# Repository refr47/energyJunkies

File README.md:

# Content

Es soll ein Produkt (HW, SW) geschaffen werden, welches analog dem [Ohmpilot von Fronius](https://www.fronius.com/de/solarenergie/installateure-partner/technische-daten/alle-produkte/l%C3%B6sungen/fronius-w%C3%A4rmel%C3%B6sung/fronius-ohmpilot/fronius-ohmpilot) funktioniert. Damit soll überschüssiger PV-Strom hausintern verbraucht werden (z.B. Warmwasseraufbereitung). Als Steuerzentrale wird ein uController - [esp32 mit kleinem Display](https://www.lilygo.cc/products/lilygo%C2%AE-ttgo-t-display-1-14-inch-lcd-esp32-control-board) - herangezogen. Dieser ESP ist mit WLAN und Bluetooth ausgestattet. Als ReferenzWR werden Fronius-WR herangezogen, wobei hier der Modbuszugang freizuschalten ist. 

## Installation /InBetriebnahme / Fehler
Unter [https://github.com/htlWels/energyJunkies/blob/main/projects/sware/ohmPilotFronius/doc/install.md] ist eine Installationsanleitung zu finden, welche die einzelnen Schritte für eine erfolgreiche Installation Schritt für Schritt erläutert.
Es können natürlich noch Fehler oder seltsames Verhalten auftreten. Diese könnten unter [https://github.com/htlWels/energyJunkies/blob/main/projects/sware/ohmPilotFronius/doc/error.md] dokumentiert werden und werden dann behoben. 

## Versionsverwaltung per GIT
Die installierbaren Versionen werden im "main"-Branch verwaltet und die Erweiterungen in einem separaten Branch. Nach einem erfolgreichen Test werden dann die Branches wieder in den Main-Branch integriert und die Version wird dann erhöht. Es wird mit der Version v0.9 bekommen

- Branch main: Basisfunktionalität (Heizstab-Regler mit Untersützung des Fronius-WR und AMIS-Reader (Siemens TD3511 Smartmeter), Temperaturüberwachung, minimaler Shelly-Support
- Branch shelly: Experimentielles im Umgang  mit Shelly-Produkten
- Branch enj: Testumgebung für ENJ für das Austesten der 4 Buttons
- Branch Powerregulation: kl. Beispiel von Bernhard für pid-Regler
- Branch loxone: Erweiterung des REST-Interfaces für Einbindung Loxone-Verwaltung, Reduzierung des Codes auf die Ansteuerung der Platine, kein Modbus/Fronius/amisReader-Support

## Anforderungen

Das Produkt wird in einen hardware- und softwareabhängigen Teil aufgespaltet. Es ist ein "Hobby"-Projekt, aber dennoch sollten die wesentlichen Anforderungen erfasst werden. Prinzipiell wird davon ausgegangen, dass die zu betreibenden Heiz/Lade -elemente einen 3-phasigen Anschluß haben, die dann einzeln angesteuert werden.

### HW

Der OhmPilot von Fronius kann dzt. um die gut € 1.000,-- erworben werden, d.h. die Entwicklungskosten für die HW sollten deutlich unterschritten werden (!)

* Die GPIOs des ESP32 werden mit 3.3 V betrieben. Über eine entsprechende TransistorSchaltung kann je Phase dann per Relais durchgeschaltet werden. Alternativ könnte ein Pegelwandler 3.3V auf 5V genutzt werdenererer
* 2 Temperatursensoren sorgen für einen "Not-Aus", d.h. wenn beispielsweise das Wasser schon 85° hat, darf nicht mehr geheizt werden. Sicherheitshalber werden 2 Sensoren verwendet für den Fall, dass einer ausfällt. Die gesteuerte Last könnte auch indirekt über ein Sicherheitsthermostat indirekt angeschlossen werden.
* Lage des Displays (vertikal | horizontal) ?
* Vorschläge von Ej - Blockschaltbilder liegen in **projects/ohmPilotFronius/**
* EJ-EMV Filter (Elektromagnetischer Filtervorsatz, auf diesen wird in der ersten Phase verzichtet bzw. Vorversuche gestartet)
-  EJ-Control Board (ESP32 TTGO, Eingabe, Ausgabe Schnittstellen, Versorgt über die Power Unit)
-  EJ-Power Unit1 (Phasenanschnitt mit Modul 2-10V vom Armin bzw. Modul 0-20mA vom Oliver, sehr große EMV Probleme, erste Hardware für Versuche)
-  EJ-Power Unit2 (PWM Endstufe, eventuell Schülerprojekt 23/24, große EMV Probleme)
-  EJ-Power Unit3 (Pulspakete, eventuell Schülerprojekt 23/24, wenig EMV Probleme, AMIS Zähler?)
-  EJ-Power Unit4 (eine Art 7 Takt Schaltung wie bei den alten E-Herd Platten, sehr wenig EMV Probleme, keine stufenlose Regelung)

#### Verbesserungsvorschläge
- Rote LED, welche eine Warnung/Fehler anzeigt; dieser wird zusätzlich am Display angezeigt
- die dzt. 4 Taster sollten mit einer Brücke einstellbar sein ; somit stehen 4 GPIOs zur Verfügung, die anderweitig eingesetzt werden können (potentialfreie Ausgänge, über Buchse ausführen
- PWM Verbindung herstellen (bei neuer Platine)
- 4 Schalter abänderung und verwenden für
  * S1: Zustands-/Fehler LED
  * S2: Relais ausführen
  * S3/S4: eventuell die anderen 2 auch als potentialfreien Ausgang ausführen (Relais)
- Shelly Einbindung (reine SW)

### SW

* Setup: Folgende Parameter sind benutzer- bzw. analagenabhängig:
  - Einstellung der WLAN-Zugangsdaten (SSID,Password)
  - IP-Adresse Modbus
  - Heizstableistung (für die rechnerische Festlegung der in das Heizsystem geleiteten Energie)
  - Einspeisebeschränkung (wieviel kW dürfen eingespeist werden)
 -  <del>PI-Regler für den 0-100 % Ausgang (Proportional(P),Integral(I),Differenzial(D)) - Default: P=1, I=0.5, D=0 (FLoat)</del>
  - <del>Regelbereich Hysterese für die PWM-Steuerung (z.B. 5.900, 5.800 - Hysterese: 100) - oder von Einspeisebeschränkung 100 Watt abziehen und Hysteresewert </del>
  - Für die Eingabe ist eine WebSite zu verwenden, wobei der uController (ESP32) bei der Erst-Inbetriebnahme oder Wechsel des Wlan-Einwählpunktes als AccessPoint fungiert. Die notwendigen Informationen (SSID,IP-Adresse) sind per Display anzuzeigen.
  - Die Setup-Basisdaten sind per EEProm zu sichern, die bei einem Restart dann herangezogen werden können. 
* Auf dem Display sollten die wichtigsten Informationen angezeigt werden können:
  - aktive Netzwerkverbindung
  - IP-Adresse
  - aktuelle Produktion, davon Überschuss
  - Zuteilung an die 3 Phasen
  - aktuelle Temperatur des Wasses, gemessen durch die 2 TempSensoren
  - Fehler
  - ?
* Die Kommunikation wird per WLAN durchgeführt, wobei regelmäßig zu prüfen ist, ob die WLAN-Verbindung noch funktioniert
  - ?? hat nur tagsüber Sinn
  - was passiert, wenn die Kommunikation nicht mehr funktioniert - Fehlermeldung am Display ( ! ), Abschalten des Reglers für den Heizstab
- Der WR wird per Modbus (TCP) angesteuert & setzt eine funktionierende WLAN-Verbindung voraus.
- Alternativ kann auch der AmisReader verwendet werden, wobei hier weniger Informationen zur Verfügung stehen. 
- Da Fronius bei der kostenlosen Variante die Verbrauchsdaten nur für 3 Tage loggt, kann der ESP32 diese mitloggen. Dafür ist jedoch ein CardReader notwendig.
- kleines REST-API, wo die wichtigsten Daten per Web verfügbar sind, die IP-Adresse steht ja auf dem DIsplay.
- Benachrichtigung per Email, dass irgend etwas passiert ist ( ? )
- Der Regler muss bei Erreichen des Temperaturlimits (per Setup-Dialog einstellbar) sämtliche Kanäle abschalten.
- Sofern ein Akku vorhanden ist, soll die Priorisierung einstellbar sein (d.h. wird zuerst der Boiler oder der Akku geladen).

## Offene Fragen
* Initialisierung/sETUP: Wenn Netzwerk nicht funktioniert, kommt man automatisch in den AccessPoint-Modus;
* ```Wenn beim Setup kein gültiges WLAN-Netzwerk vorgefunden wird, bootet der ESP32 im AP-Modus mit der Default-Adresse 192.168.4.1 und bietet dazu auch einen offenen Zugang namens "EnergyJunkies" an.```
* Was macht man bei auftretenden Fehlern?
* ```Diese werden sowohl am Display als auch am Web-Interface angezeigt.```

## Was einem sonst noch so einfällt

* Bezüglich Tag/Nacht-Betrieb: Prinzipiell macht die Steuerung nur dann Sinn, wenn Strom produziert wird -also tagsüber. Wahrscheinlich werden künftig unterschiedliche h-Strompreise angeboten werden, d.h. bei schönem Wetter ist mehr Solarstrom da und daher günstiger ( ? ) oder der Strom ist dann teuerer, wenn mehr gebraucht wird (z.B. vormittags). Einen Boiler muss man immer betreiben und hier könnte es Sinn machen, auch einen Nachtbetrieb einzuführen, da hier der Strom wahrscheilich günstiger ist.
* Es wäre für die Optimierung der Energiekosten (welcher Tarif ist für das Aufheizen/Aufladen am günstigsten) günstig, wenn man den Wetterbericht kennt, denn dann weiß man ja, ob genug Solarstrom vorhanden ist, den Task durchzuführen (z.B. Aufladen).
* Künftig werden wahrscheinlich variable Einspeistarife vorgegeben werden, variable Stromkosten für den Einkauf gibt es ja schon. Hier kann dann optimiert werden in Abstimmung mit einem eventuell vorhandenen Akku, wann wer wie geladen / in das Netz gespeist wird.
* Poolpumpe bzw. Poolwärmepumpe: Poolpumpe wälzt das Wasser im Becken um, egal welche Qualität das Wasser hat. Hier könnte in Verbindung mit einem Frequenzumformer die Leistung der Pumpe reduziert werden, wenn man weiß, welche Qualität das Wasser dzt. hat. Die Wärmepumpe kann ebenfalls in Abhängigkeit von Überstrom gesteuert werden (Ein- bzw. Ausschalten per TCP?)
* Setup: Jeder hat ja seine eigen Zugangsdaten - wie sollen diese am Besten berücksichtigt werden. Der geringste Aufwand ist die Erstellung eines eigenen setup.h-Files, in der sämtliche spezifische Daten eingetragen werden. Elegant wäre natürlich das Setup per Handy, wobei der ESP im Setup-Modus bootet und einen eigenen AP zur Verfügung stellt, in der sich eine App einwählt und dann die Zugangsdaten einstellt. Diese Daten werden dann ins Eprom verfrachtet - ``Ẁird so durchgeführt``
* Im Prototyp sind ja 4 zusätzliche Taster vorgesehen - es ist hier zu definieren, welche Funktionalität hier hinterlegt wird.
* Thema WLAN/Setup: ich hab bereits ein Projekt mit einem ESP2866 am Start und genau diese Problematik. Ich hab 2 Bibliotheken im Einsatz: 
  - [WIFI-Manager](https://github.com/tzapu/WiFiManager) Hotspot + Webserver für WLAN Konfiguration + eigenes Setup möglich (ums Speichern des eigenen Setups muss man sich selbst kümmern)
  * [WebConfig](https://github.com/GerLech/WebConfig)eigener Webserver ausschließlich für Konfiguration, Daten werden am FS gespeichert
* HomeKit Integration: ich hab bereits etliche Geräte mit Apple HomeKit im Einsatz und auch schon eigene Geräte HomeKit tauglich gemacht. Meine Idee wäre, einfach einen Schalter mit einem ESP zu simulieren (z.B. Stromüberproduktion-> Schalter ist ON, ...) Dieser Schalter lässt sich easy in die bestehende Infrastruktur einbinden und dank Homekit können dann eigene Abläufe konfiguriert werden -> "Schalter Stromüberproduktion" = ON -> schalte über einen Shelly (ebenfalls mit Homekit Firmware geflasht) den Warmwasserboiler ein. ```Zum Verständnis: HomeKit frägt die Steuerung periodisch ab und gibt dann - je nach vorhandenem Strom - ein "On" oder "Off" zurück - Schwelle für "On" (also wieviel (k)Watt) ist einstellbar```
* Shelly-Support: Die Shelly-Infrastruktur ist bezüglich Wachstum recht viral und Shelly bietet neben einer funktionierenden App auch ein REST- und MQTT-Interface an. Shelly brauchen eine intakte WLAN-Verbindung und schalten ab, wenn kein Netzwerk verfügbar ist (z.B. Abschalten während der Nachtstunden). Man muss Shelly dann manuell per App einschalten - ein Reconnect wird dzt. nicht unterstützt. 

# IDE/PlatformIO

<ol>
    <li>[C/C++ COmpiler mit Platformio](https://alsaibie.github.io/embedded_ccpp/ide_setups/pio_for_host/)
    </li>
</ol>
## Links & Foren
<ol>
<li>
Photovoltaik Form [Photovoltaik Form](https://www.photovoltaikforum.com/thread/50214-gen24-modbus-tcp/)
</li>
    <li>
        [TTGO ESP] (https://www.lilygo.cc/products/lilygo%C2%AE-ttgo-t-display-1-14-inch-lcd-esp32-control-board)
    </li>
    <li>
        Mark Down Formatierung (https://www.markdownguide.org/cheat-sheet/#extended-syntax)
    </li>

</ol>

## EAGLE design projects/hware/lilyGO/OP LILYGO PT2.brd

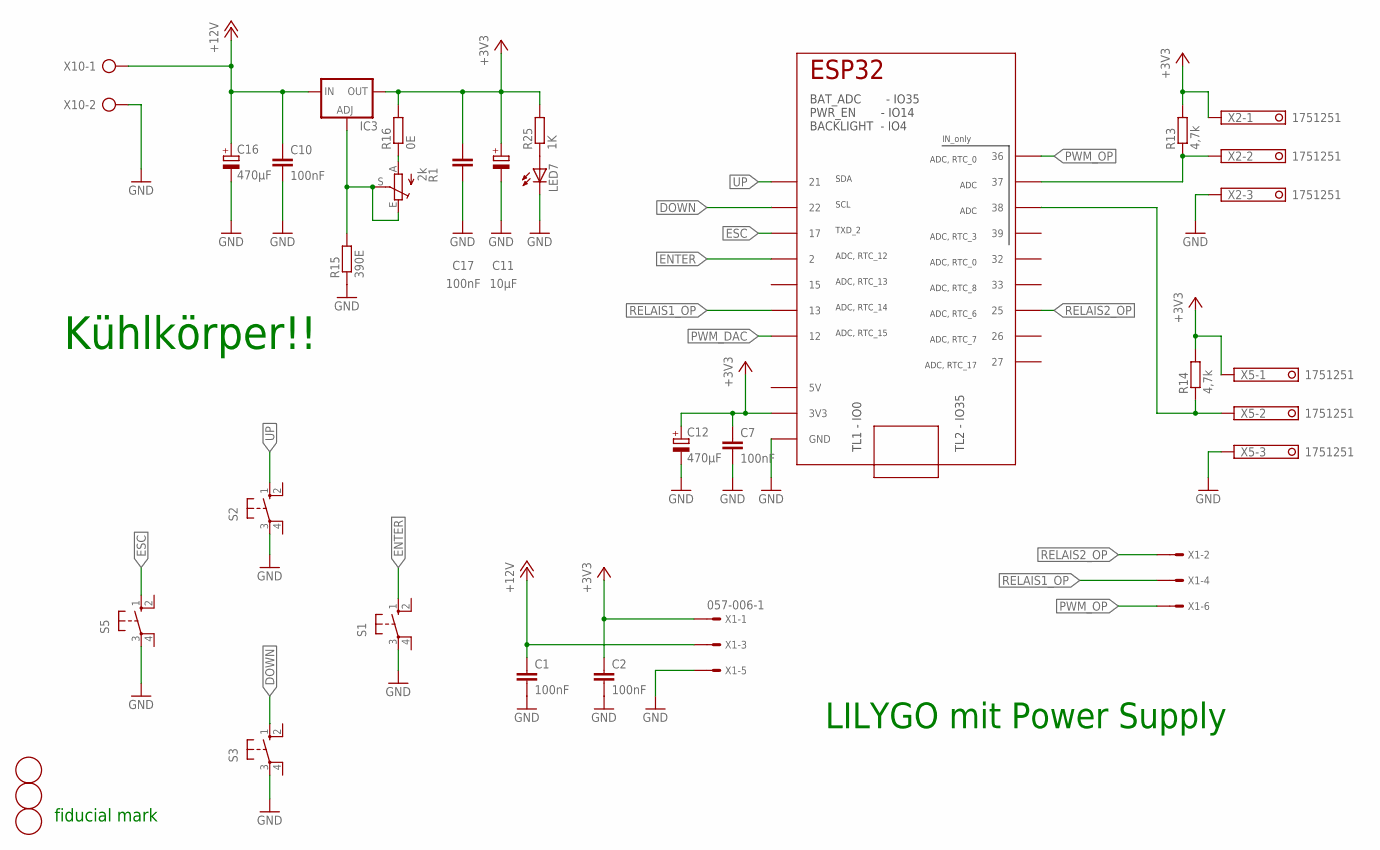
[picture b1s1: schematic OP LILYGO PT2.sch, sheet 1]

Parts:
C1, C2, C7, C10, C17: 100nF; C025-030X050
C11: 10µF; E2,5-6
C12, C16: 470µF; E2,5-6
IC3: LM317TS; 317TS
IC4: TTGO_DISP; TTGO_DISP_DEFAULT
LED7: LED5MM
R1: 2k; S64YW
R13, R14: 4,7k; 0207/12
R15: 390E; 0207/12
R16: 0E; 0207/12
R25: 1K; 0207/12
S1, S2, S3, S5: 10-XX; B3F-10XX
U$2, U$7, U$8: FIDUCIALMOUNT; FIDUCIA-MOUNT
X1: 057-006-1
X2, X5: 1751251
X10: SMKDSP_1,5/2

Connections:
+3V3: C2.1, C7.1, C11.+, C12.+, C17.1, IC3.2 (OUT), IC4.3V3_1 (3V3), IC4.3V3_2 (3V3), R13.2, R14.2, R16.2, R25.2, X1.1, X2.1, X5.1
+12V: C1.1, C10.1, C16.+, IC3.3 (IN), X1.3, X10.1; also elsewhere on the board
DOWN: IC4.22, S3.1 (S)
ENTER: IC4.2, S1.1 (S)
ESC: IC4.17, S5.1 (S)
GND: C1.2, C2.2, C7.2, C10.2, C11.-, C12.-, C16.-, C17.2, IC4.GND_1 (GND), IC4.GND_2 (GND), IC4.GND_3 (GND), IC4.GND_4 (GND), IC4.GND_5 (GND), LED7.K (C), R15.1, S1.3, S2.3, S3.3, S5.3, X1.5, X2.3, X5.3, X10.2; also elsewhere on the board
unnamed: IC3.1 (ADJ), R1.E, R1.S, R15.2
unnamed: R1.A, R16.1
unnamed: IC4.37, R13.1, X2.2
unnamed: IC4.38, R14.1, X5.2
unnamed: LED7.A, R25.1
PWM_DAC: IC4.12; also elsewhere on the board
PWM_OP: IC4.36, X1.6
RELAIS1_OP: IC4.13, X1.4
RELAIS2_OP: IC4.25, X1.2
UP: IC4.21, S2.1 (S)

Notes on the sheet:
LILYGO mit Power Supply
fiducial mark
Kühlkörper!!

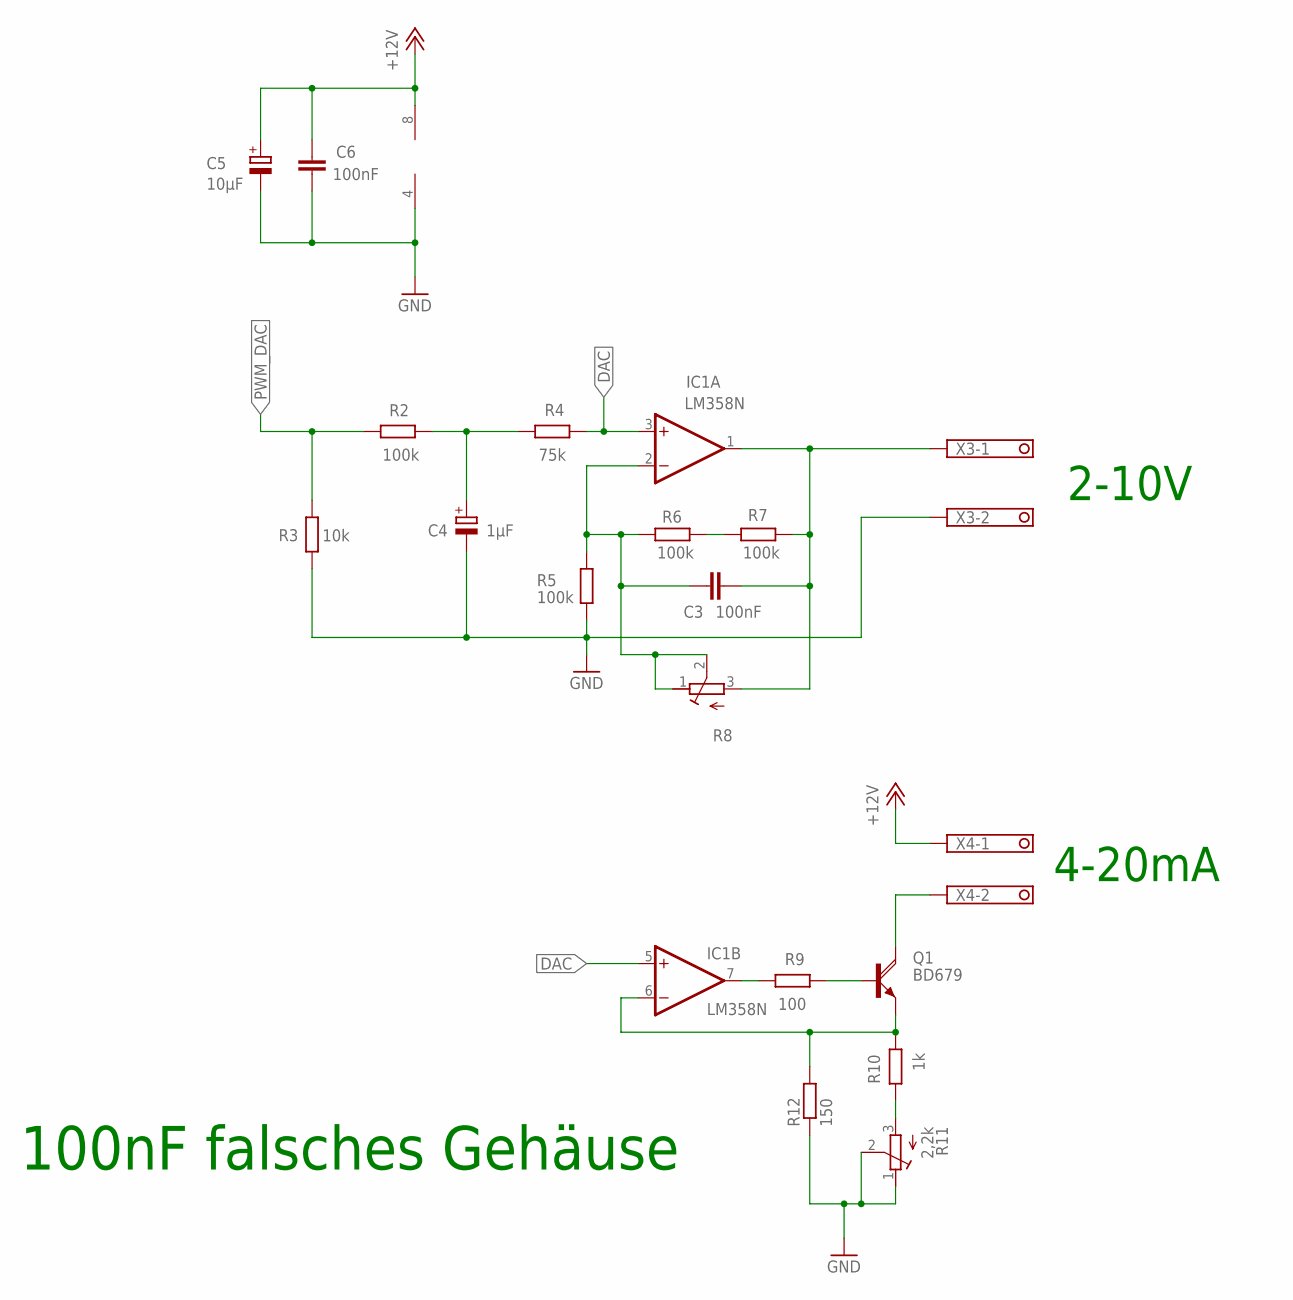
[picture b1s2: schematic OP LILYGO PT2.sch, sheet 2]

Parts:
C3, C6: 100nF; C050-035X075
C4: 1µF; E2,5-5
C5: 10µF; E2,5-5
IC1: LM358N; DIL08
Q1: BD679; TO126AV
R2, R5, R6, R7: 100k; 0207/2V
R3: 10k; 0207/2V
R4: 75k; 0207/2V
R8: R-TRIMMT93YA; RTRIMT93YA
R9: 100; 0207/10
R10: 1k; 0207/2V
R11: 2,2k; RTRIMT93YA
R12: 150; 0207/12
X3, X4: 1751248

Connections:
+12V: C5.+, C6.1, IC1.8 (V+), X4.1; also elsewhere on the board
DAC: IC1.3 (+IN), IC1.5 (+IN), R4.1
GND: C4.-, C5.-, C6.2, IC1.4 (V-), R3.1, R5.2, R11.1 (E), R11.2 (S), R12.1, X3.2; also elsewhere on the board
unnamed: C3.1, IC1.2 (-IN), R5.1, R6.1, R8.1 (E), R8.2 (S)
unnamed: C4.+, R2.2, R4.2
unnamed: R10.2, R11.3 (A)
unnamed: C3.2, IC1.1 (OUT), R7.2, R8.3 (A), X3.1
unnamed: R6.2, R7.1
unnamed: IC1.6 (-IN), Q1.E, R10.1, R12.2
unnamed: Q1.B, R9.1
unnamed: IC1.7 (OUT), R9.2
unnamed: Q1.C, X4.2
PWM_DAC: R2.1, R3.2; also elsewhere on the board

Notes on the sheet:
2-10V
4-20mA
100nF falsches Gehäuse

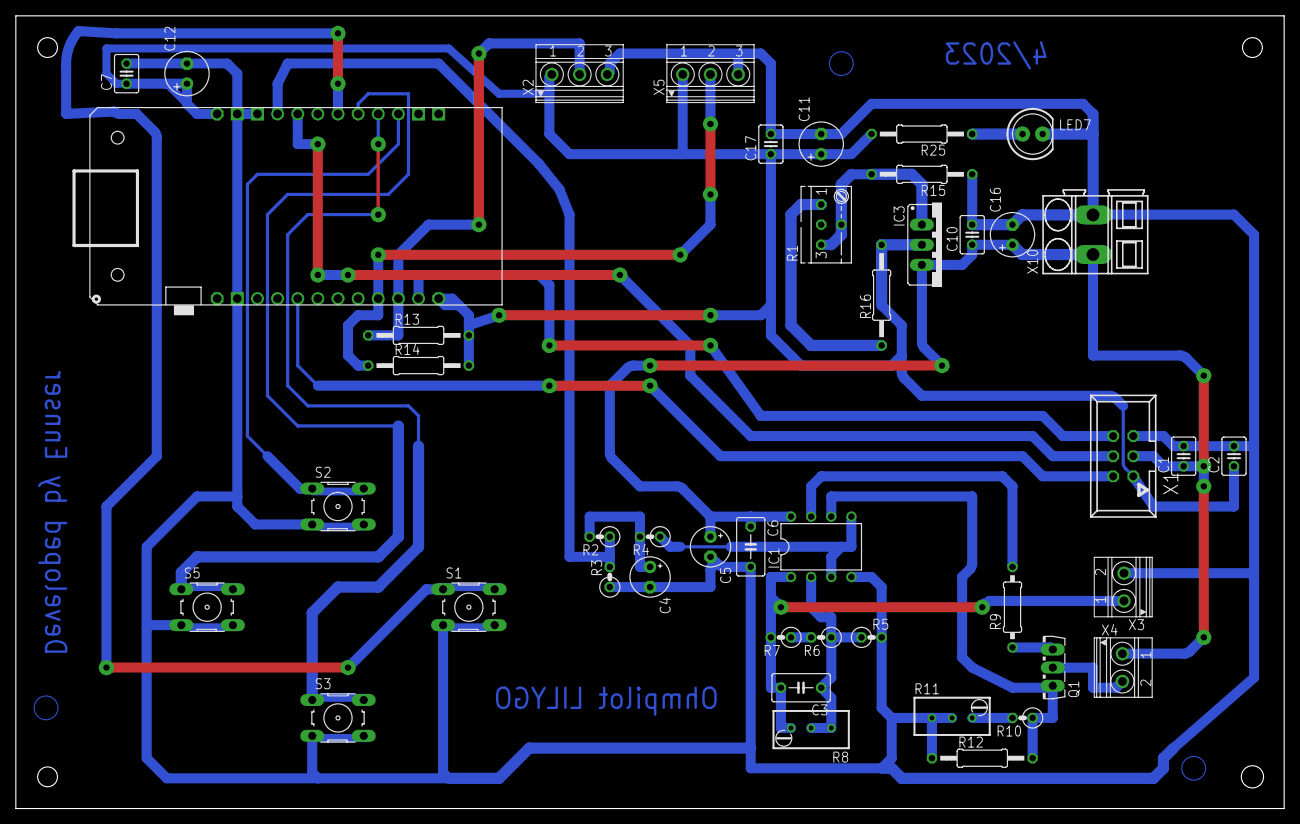
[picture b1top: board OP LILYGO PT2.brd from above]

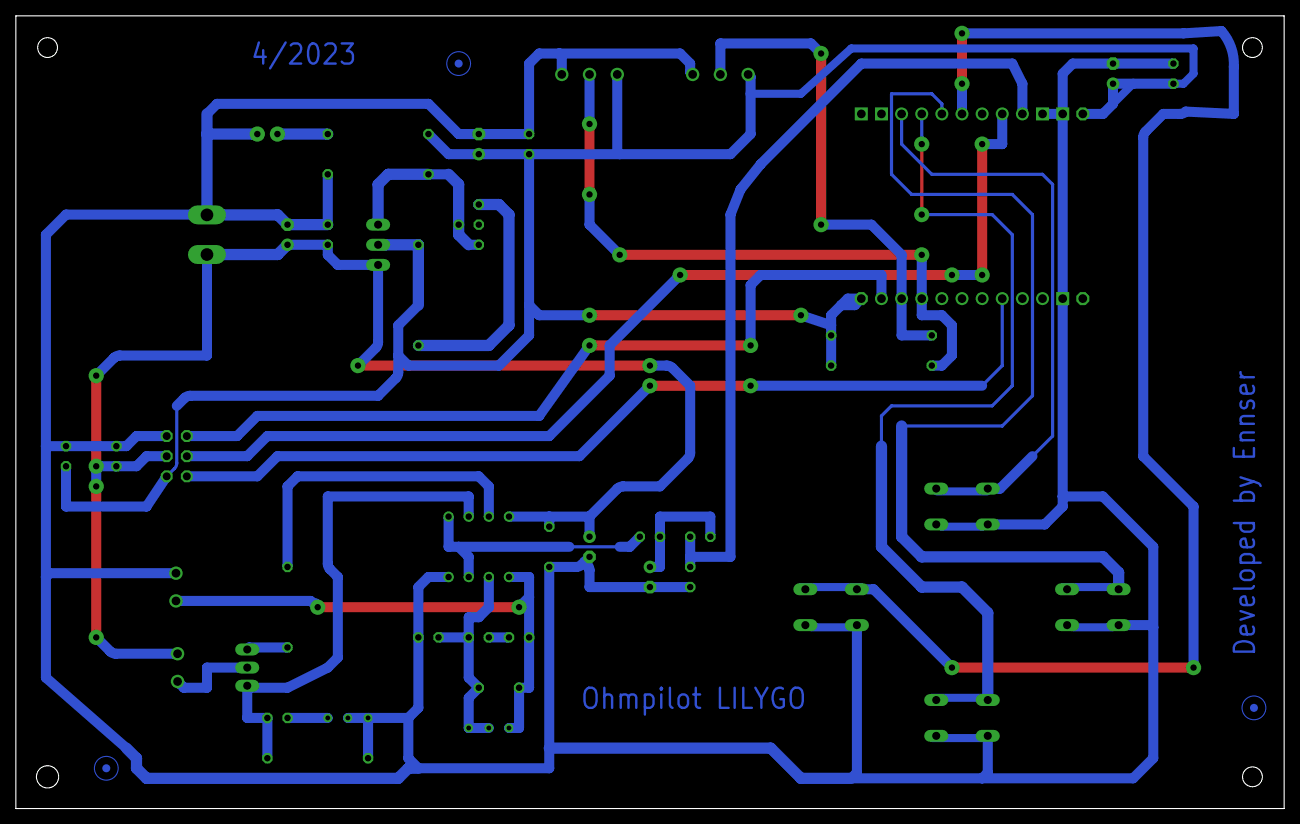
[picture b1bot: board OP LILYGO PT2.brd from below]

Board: 2 copper layers, 160.0 x 100.0 mm, 47 parts (3 on the bottom side), 26 nets.

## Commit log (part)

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2024-02-02 controller
2024-02-02 huawei
2024-02-02 fronius
2024-02-04 amisReader
2024-02-04 amis
2024-02-05 websock
2024-02-05 main
2024-02-06 setup
2024-02-07 states
2024-02-07 solar
2024-02-12 defines/remove string
2024-02-15 sockets
2024-02-19 debug
2024-02-19 bugfix, debugger
2024-02-21 froniusSolar
2024-02-21 socket
2024-02-21 bug fix
2024-02-21 output.js
2024-02-22 defines
2024-02-22 index
2024-02-23 energieManager
2024-03-14 http-get-request
2024-03-20 wheater
2024-04-21 eeprom
2024-04-23 eprom
2024-04-25 utils
2024-04-26 pidManager
2024-04-29 temp
2024-05-10 heap
2024-05-10 wwww
2024-05-12 wlan
2024-05-12 nain
2024-05-13 shelly
2024-05-13 install
2024-05-13 install.md
2024-05-13 error
2024-05-19 Doku
2024-05-22 logReader
2024-05-22 logWWW
2024-05-22 logswww
2024-05-31 esp log lib
2024-07-09 'NetzOOE-Export zu Lastprofil'-Generator
    Skript erzeugt aus einem Viertelstunden-Protokoll (z.B. von Netz OÖ) ein Lastprofil für z.B. den Tarifkalkulator der E-CONTROL.
2024-07-26 shelly,web
2024-07-26 shelly-eprom
2024-07-26 amisReader / interpretation output pidController
2024-07-26 docker
2024-07-26 merge
2024-07-26 script
2024-08-03 fixError(wlan,pidManager)
2024-08-04 fixError
2024-08-12 mqtt
2024-08-22 reconnect
2024-10-10 temp sensor
2024-10-11 loxone
2024-10-11 ajax
2025-06-07 tempenumberOfDevicesratur
2025-06-07 oneWire
2025-08-03 temperature control
2025-08-04 overflow temperature
2025-08-29 refactor: clean up code structure and improve readability
2025-08-30 ajaxCall,update, strncpy
2025-08-31 pidmanager, reset, clear pwm
2025-09-02 amisreader,websocket: error fixing
2025-09-02 ajaxCall,handle_store as callback from update stammdaten
2025-09-05 ajaxCall, update - fixing errors
2025-09-29 Wetter Prognose Modell
2026-03-23 bug fixes
2026-03-23 buf fixes
2026-03-23 clang
2026-03-26 refactoring
2026-03-27 pinManager
2026-03-28 pid regler
2026-03-28 pid, www
2026-03-28 ajaxWeb
2026-04-01 Log Macros, float2string, PID-Manager
2026-04-02 client
2026-04-04 Client vue
2026-04-04 login
2026-04-05 log anzeigen
2026-04-06 LittleFS, client
2026-04-07 WebServer
2026-04-08 task, ai
2026-04-10 vTask
2026-04-12 client bug fix
2026-04-12 client, bug fix
2026-04-15 bugFix
2026-04-17 2 phasen Erweiterung
2026-04-25 Eeprom, ajaxCalls
2026-04-25 Template
2026-04-27 Templates, KI, Phasenmanagement
2026-04-27 platform.io
2026-04-27 2 phasen
2026-04-27 node_modules endgültig entfernt und ignoriert
2026-04-28 HomeView
2026-05-01 logView
2026-05-02 pidManager,2Phasen
2026-06-19 Bug fixing, Network reconnect
